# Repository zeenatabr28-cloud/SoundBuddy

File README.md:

# SoundBuddy

WHAT? :
An ESP32-C3 based MP3 Player with a fun rococo feel.

WHY? :
I love the isea of deviding your smartphone into multiple "dumb" devices, as this allows for less distraction overall and brings you back to a simpler time.

SCREENSHOTS! :

Schematic :

Case :

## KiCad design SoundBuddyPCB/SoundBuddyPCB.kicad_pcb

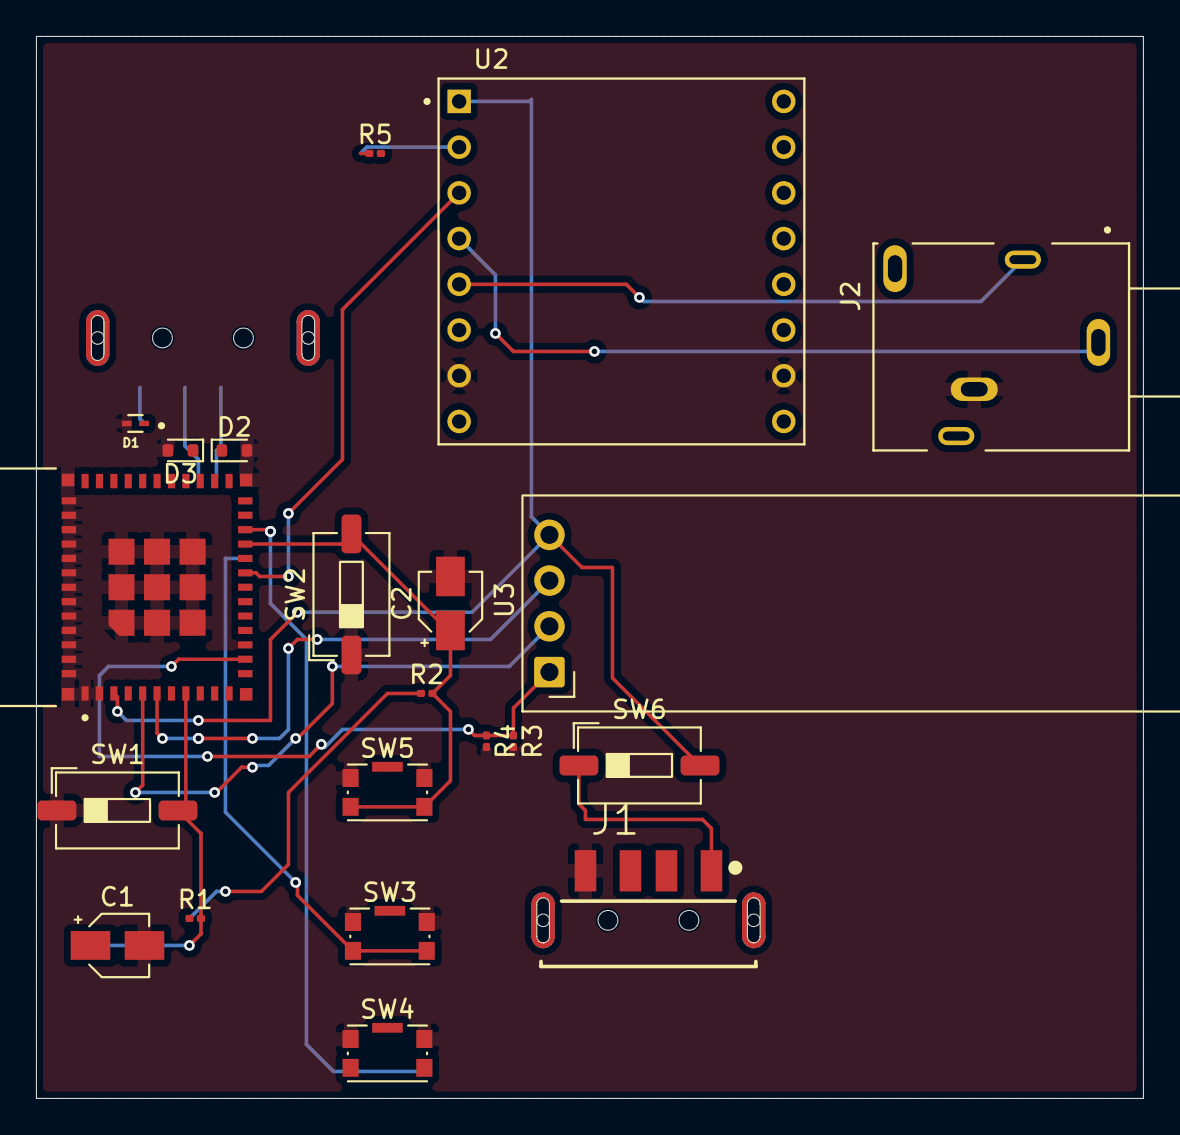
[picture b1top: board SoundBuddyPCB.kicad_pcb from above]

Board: 2 copper layers, 61.5 x 59.0 mm, 22 parts (1 on the bottom side), 18 nets.

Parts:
C1, C2: 1uf; CP_Elec_3x5.3
D1: ESD9X5.0ST5G; SODFL1006X43N
D2, D3: ESD5Zxx; D_SOD-523
J1, J3: USB1061-XX-X-X_REVA; GCT_USB1061-XX-X-X_REVA
J2: PJ324M; WENZHOU_PJ324M
R1, R2, R5: 10k; R_0201_0603Metric
R3, R4: 100k; R_0201_0603Metric
SW1, SW2: SW_DPST_x2; SW_DIP_SPSTx01_Slide_6.7x4.1mm_W6.73mm_P2.54mm_LowProfile_J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
SW3, SW4, SW5: SW_Push; SW_Push_1P1T-SH_NO_CK_KMR2xxG
SW6: SW_SPST; SW_DIP_SPSTx01_Slide_6.7x4.1mm_W6.73mm_P2.54mm_LowProfile_J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
U1: ESP32-C3-MINI-1-N4; XCVR_ESP32-C3-MINI-1-N4
U2: DFR0299; MODULE_DFR0299
U3: ER_OLEDM0.91_1x-I2C

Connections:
+3.3V: R1.1, R2.1
GND: C1.2, C2.2, D1.A, D2.2 (A), D3.2 (A), J1.4 (GND), J1.5 (SHIELD), J1.6 (SHIELD), J2.3, J3.4 (GND), J3.5 (SHIELD), J3.6 (SHIELD), R3.2, R4.2, SW1.1 (A), SW2.1 (A), SW3.1, SW4.1, SW5.1, U1.1 (GND), U1.2 (GND), U1.11 (GND), U1.14 (GND), U1.36 (GND), U1.37 (GND), U1.38 (GND), U1.39 (GND), U1.40 (GND), U1.41 (GND), U1.42 (GND), U1.43 (GND), U1.44 (GND), U1.45 (GND), U1.46 (GND), U1.47 (GND), U1.48 (GND), U1.49_1 (GND), U1.49_2 (GND), U1.49_3 (GND), U1.49_4 (GND), U1.49_5 (GND), U1.49_6 (GND), U1.49_7 (GND), U1.49_8 (GND), U1.49_9 (GND), U1.50 (GND), U1.51 (GND), U1.52 (GND), U1.53 (GND), U2.7 (GND), U2.10 (GND)
unnamed: J1.1 (VBUS), SW6.1 (A)
unnamed: C1.1, R1.2, SW1.2 (B), U1.8 (EN)
unnamed: C2.1, R2.2, SW2.2 (B), SW5.2, U1.21 (IO7)
unnamed: SW6.2 (B), U1.3 (3V3), U2.1 (VCC), U3.4 (SDA)
unnamed: R3.1, R4.1, U1.13 (IO1), U3.1 (GND)
unnamed: U1.5 (IO2), U3.2 (VCC)
unnamed: U1.6 (IO3), U3.3 (SCL)
unnamed: U1.19 (IO5), U2.3 (TX)
unnamed: SW3.2, U1.20 (IO6)
unnamed: SW4.2, U1.22 (IO8)
unnamed: J2.5, U2.5 (DAC_L)
unnamed: J2.1, U2.4 (DAC_R)
unnamed: R5.1, U2.2 (RX)
USB+: D3.1 (K), J3.3 (D+), U1.27 (IO19)
USB-: D2.1 (K), J3.2 (D-), U1.26 (IO18)
VBUS: D1.C, J3.1 (VBUS)
